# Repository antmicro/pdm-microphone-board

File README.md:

# Microphone board

Copyright (c) 2024-2025 [Antmicro](https://www.antmicro.com)

## Overview

This project contains open hardware design files for a microphone board with an SPH0644LM4H-1 PDM microphone.
The board break-routes PDM signals from the microphone to a zero insertion force connector.
Additionally, the board provides voltage filtering and ESD protection.

The design files were prepared in KiCad 8.x.

## Key features

* Knowles [SPH0644LM4H-1](https://www.mouser.com/datasheet/2/218/ph0644lm4h-1_revc-1518995.pdf)
* Zero insertion force connector for a 5 pin, 0.5 mm pitch FFC
* Selectable Left or Right channel audio transmitting
* Designed to fit an 11mm diameter opening
* Alignment cutouts for toolless mounting 

## Project structure

The main directory contains KiCad PCB project files, a LICENSE, and a README.
The remaining files are stored in the following directories:

* `doc` - contains schematics in PDF format
* `assets` - contains visual assets for showcasing this design on [Open Hardware Portal](https://openhardware.antmicro.com) and [System Designer](https://designer.antmicro.com)

## Licensing

This project is published under the [Apache-2.0](LICENSE) license.

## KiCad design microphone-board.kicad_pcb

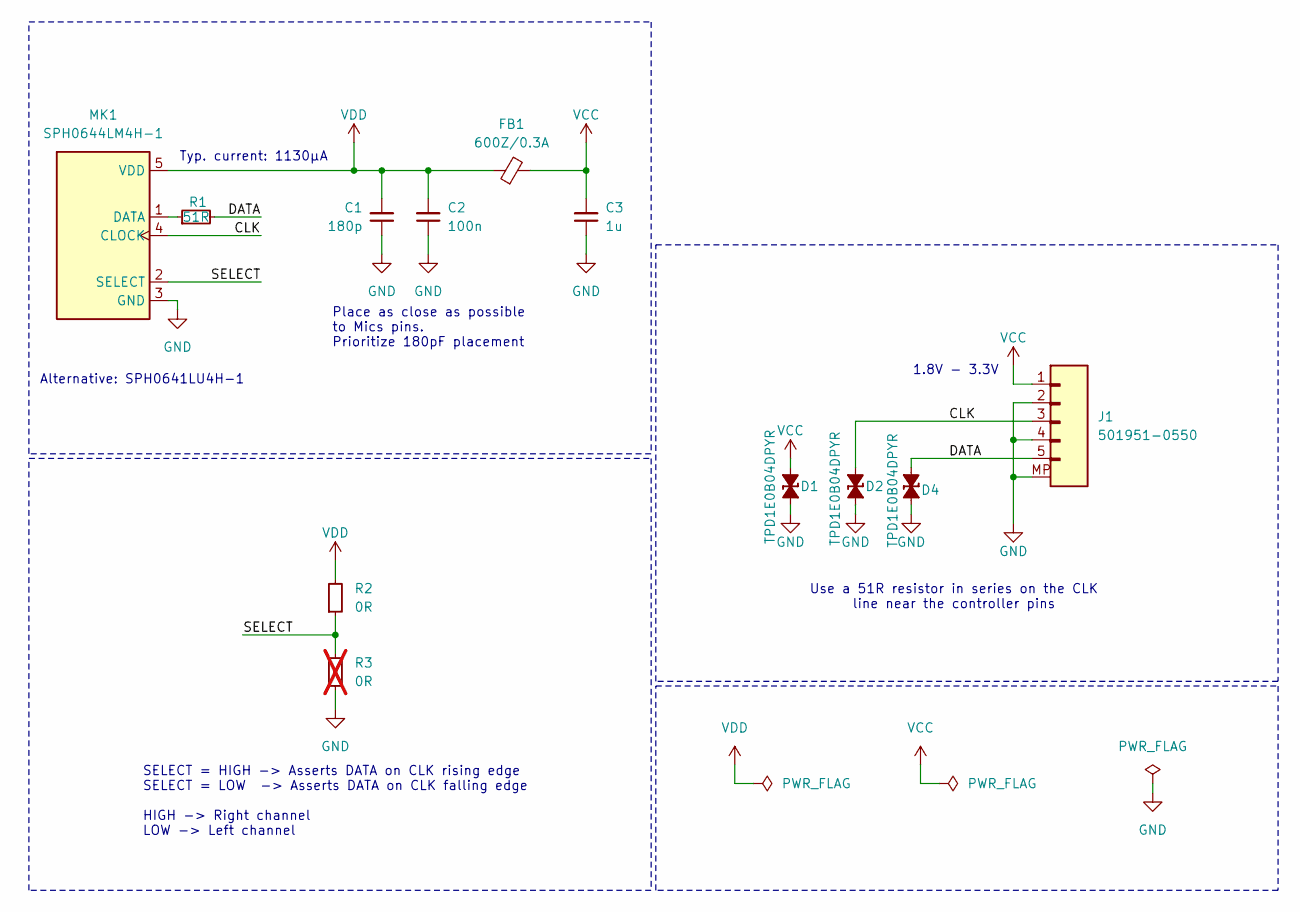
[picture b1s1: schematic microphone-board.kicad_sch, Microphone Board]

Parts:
C1: C_180p_0402; C_0402_1005Metric; MPN 04025A181JAT2A
C2: C_100n_50V_X8L_0402; C_0402_1005Metric; Voltage 50V; MPN GCM155L8EH104KE07D
C3: C_1u_0402; C_0402_1005Metric; MPN C1005X6S1A105K050BC
D1, D2, D4: TPD1E0B04_XDFN-2; XDFN-2_1x0.60mm; MPN TPD1E0B04DPYR
FB1: FB_600Z_0.3A_Murata-BLM15AG_0402; FB_0402_1005Metric; MPN BLM15AG601SN1D
J1: Conn_FFC_Molex_5019510550; MPN 501951-0550
MK1: MK_SPH0644LM4H-1; MPN SPH0644LM4H-1
R1: R_51R_0402; R_0402_1005Metric; Tolerance 1%; MPN CR0402-FX-51R0GLF
R2: R_0R_0402; R_0402_1005Metric; MPN ERJ2GE0R00X
R3: R_0R_0402; R_0402_1005Metric; MPN ERJ2GE0R00X; not fitted

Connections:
/CLK: D2.1 (C), J1.3, MK1.4 (CLOCK)
/DATA: D4.1 (C), J1.5, R1.2
/SELECT: MK1.2 (SELECT), R2.1, R3.2
GND: C1.1, C2.1, C3.1, D1.2 (A), D2.2 (A), D4.2 (A), J1.2, J1.4, J1.MP, MK1.3 (GND), R3.1
unnamed: MK1.1 (DATA), R1.1
VCC: C3.2, D1.1 (C), FB1.2, J1.1
VDD: C1.2, C2.2, FB1.1, MK1.5 (VDD), R2.2

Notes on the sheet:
1.8V - 3.3V
Use a 51R resistor in series on the CLK line near the controller pins
Place as close as possible to Mics pins. Prioritize 180pF placement
Alternative: SPH0641LU4H-1
Typ. current: 1130µA
SELECT = HIGH -> Asserts DATA on CLK rising edge SELECT = LOW -> Asserts DATA on CLK falling edge HIGH -> Right channel LOW -> Left channel

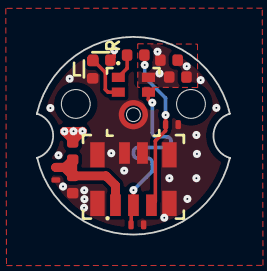
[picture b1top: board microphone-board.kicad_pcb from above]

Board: 4 copper layers, 10.7 x 11.0 mm, 12 parts (0 on the bottom side), 7 nets.

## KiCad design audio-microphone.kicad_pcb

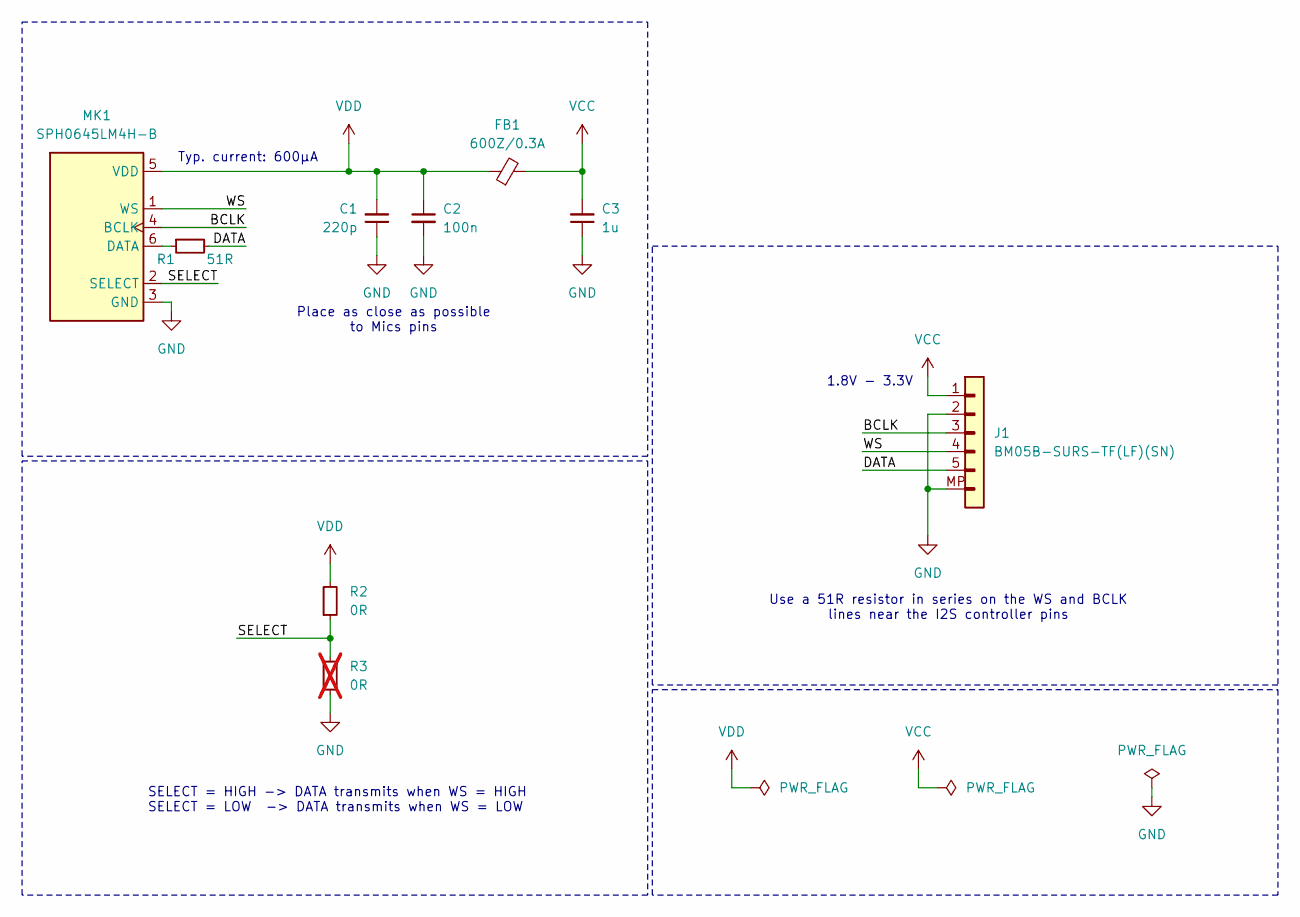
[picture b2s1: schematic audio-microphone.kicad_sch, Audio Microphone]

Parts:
C1: C_220p_0402; C_0402_1005Metric; MPN 04025C221JAT2A
C2: C_100n_0402; C_0402_1005Metric; Voltage 50V; MPN GRM155R61H104KE14D
C3: C_1u_0402; C_0402_1005Metric; MPN C1005X6S1A105K050BC
FB1: FB_600Z_0.3A_Murata-BLM15AG_0402; FB_0402_1005Metric; MPN BLM15AG601SN1D
J1: JST_SUR_1x5_BM05B-SURS-TB-LF-SN; Conn_JST_SUR_1x5_BM05B-SURS-TF-LF-SN; MPN BM05B-SURS-TF(LF)(SN)
MK1: MK_SPH0645LM4H-B; MPN SPH0645LM4H-B
R1: R_51R_0402; R_0402_1005Metric; Tolerance 1%; MPN CR0402-FX-51R0GLF
R2: R_0R_0402; R_0402_1005Metric; MPN ERJ2GE0R00X
R3: R_0R_0402; R_0402_1005Metric; MPN ERJ2GE0R00X; not fitted

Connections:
/BCLK: J1.3, MK1.4 (BCLK)
/DATA: J1.5, R1.2
/SELECT: MK1.2 (SELECT), R2.1, R3.2
/WS: J1.4, MK1.1 (WS)
GND: C1.1, C2.2, C3.1, J1.2, J1.MP, MK1.3 (GND), R3.1
unnamed: MK1.6 (DATA), R1.1
VCC: C3.2, FB1.2, J1.1
VDD: C1.2, C2.1, FB1.1, MK1.5 (VDD), R2.2

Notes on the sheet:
1.8V - 3.3V
Use a 51R resistor in series on the WS and BCLK lines near the I2S controller pins
Place as close as possible to Mics pins
Typ. current: 600µA
SELECT = HIGH -> DATA transmits when WS = HIGH SELECT = LOW -> DATA transmits when WS = LOW

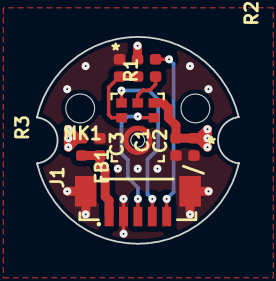
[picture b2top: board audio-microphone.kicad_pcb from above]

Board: 4 copper layers, 11.2 x 11.5 mm, 9 parts (0 on the bottom side), 8 nets.

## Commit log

2025-04-04 [#71081] Design microphone board
2025-04-04 [#71550] Update sch with SPH0645LM4H-B mic
2025-04-04 [#71550] Start placement
2025-04-04 [#71550] Update components
2025-04-04 [#71550] Update MK_SPH0645LM4H-B footprint
2025-04-04 [#71550] Add new mounting system
2025-04-04 [#71550] Swap BCLK and WS, Fix outline
2025-04-04 [#71550] Correct board outline
2025-04-04 [#71550] Change PCB to 4 layers
2025-04-04 [#71550] Route connections
2025-04-04 [#71550] Reupload assets
2025-04-04 [#71550] Change FB1 to 0402 size one BLM15AG601SN1D
2025-04-04 [#71550] Remove dash from sch name
2025-04-04 [#71986] Update connector on sch
2025-04-04 [#71550] Re-arrange components, finish routing
2025-04-04 [#71550] Limit board size to 11 mm in diameter, clear DRC
2025-04-04 [#71550] Rename and update assets
2025-04-04 [#71550] Remove unnecessary vias
2025-04-04 [#71986] Continue placement
2025-04-04 [#71550] Bump rev to 1.1.0
2025-04-04 [#71550] Remove assets
2025-04-04 [#71986] Add assets
2025-04-04 [#71986] Bump rev to 1.2.0, route connections
2025-04-04 [#71986] Add image to the README
2025-04-04 [#71986] Replace capacitors with C0G and X8L dielectrics types
2025-04-04 [#71986] Fix R3 malformed DNP properties
2025-04-04 [#71986] Update Silk L/R channels
2025-04-04 [#71986] Adjust grid and aux origin
2025-04-04 [#71986] Update zones clearance
2025-04-04 [#71986] Update date and align the name with the sch
2025-04-04 [#71986] Import Changes to the PCB, Place TVS
2025-04-04 [#72278] Bump rev to 1.3.0, Update project date
2025-04-04 [#71986] Update Rule for inner layers 0.4 mm clearance copper to edge
2025-04-04 [#71249] Update name
2025-04-04 [#71986] Add tvs protection
2025-04-04 [#71249] Update Readme
2025-04-04 [#71986] Update Assets
2025-04-04 [#71249] Update assets
2025-04-04 [#72278] Replace the microphone with MK_SPH0644LM4H-1 (PDM)
2025-04-04 [#72278] Improve power planes
2025-04-04 [#72278] Set TVS MPN to visible
2025-04-04 [#72278] Route connections
2025-04-04 [#72278] Update components from library
2025-04-04 [#72278] Update assets
2025-04-07 [#75547] Add license and logotype
2025-05-20 Review README
2025-05-20 Add PDM
2025-05-20 Notes added by 'git notes add'
2025-05-22 README: Add OSP badge
2025-05-22 [#77860] Add stackup.csv
2025-05-22 [#77860] Update assets

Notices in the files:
parts and their libraries:
License: Apache-2.0
